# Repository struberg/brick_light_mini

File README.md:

# Lightning system for game bricks

This is a game brick compatible lightning solution to control 4 LEDs.
The repo contains the controller box source code, schematic and PCB plus all the 3d printer models to create your own enclousure and lamps.
The PCB is deliberately single sided and can easily be etched by yourself with Natriumpersulfate.
Ofc if someone likes to create a double sided PCB to be made at Aisler etc then don't hesitate to ship a PR.

The schematic is based on a 0-series ATtiny-402, but a 202 will likely do fine as well.
A rechargable LiIon LIR2450 acts as power source.
The 2450 size is a good compromise between juice and size. 
Connectors are simple 2x1 Dupont types.

The only somewhat non-jellybean part is the 4x220R 0603 resistor array. 
I had to use it because 4 separate resistors would have been too big to fit on the PCB.
You can get those for very cheap from aliexpress or mouser though.

## How to connect the LEDs

You can use any standard low power white or colored LEDs.
The maximum output per LED is around 15 mA.

Place the controler box so that the button is on the lower left side and the LED connectors are on the left upper side.
The top row of the pins is all ground and internally connected.
The lower row of the pins are the positive LED pins, starting with 1 on the left side.

```
  x  x  x  x
  |  |  |  | 
  1  2  3  4  
  |  |  |  |
  x  x  x  x
```
## How to use

* single click: switch LED 1 on or off
* double click: switch LED 2 on or off
* triple click: switch LED 3 on or off
* quadruple click: switch LED 4 on or off

The device will switch off all LEDS and go to sleep after around 5 Minutes of not using the button.
This prevents emptying the battery when one forgets to turn off all lights.
The sleep current is in the µA range, I measured from 0.2µA to 1.5µA
The device will turn on again simply by pressing the button.

Have fun!

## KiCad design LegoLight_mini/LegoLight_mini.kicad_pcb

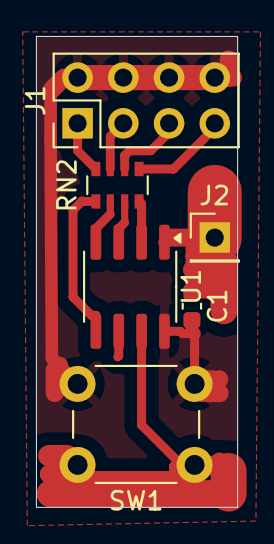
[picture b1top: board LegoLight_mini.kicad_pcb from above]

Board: 2 copper layers, 11.2 x 26.2 mm, 6 parts (0 on the bottom side), 11 nets.

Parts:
C1: 1u; C_0603_1608Metric
J1: Conn_02x04_Odd_Even; PinHeader_2x04_P2.54mm_Vertical
J2: +bat; PinHeader_1x01_P2.54mm_Vertical
RN2: 220R; R_Array_Convex_4x0603
SW1: SW_Push; SW_PUSH_6mm_H7.3mm
U1: ATtiny402-SS; SOIC-8_3.9x4.9mm_P1.27mm

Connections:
/Btn: SW1.1, U1.7 (PA3)
/L1: RN2.1 (R1.1), U1.5 (PA2)
/L2: RN2.2 (R2.1), U1.4 (PA1)
/L3: RN2.3 (R3.1), U1.3 (PA7)
/L4: RN2.4 (R4.1), U1.2 (PA6)
GND: C1.2, J1.2, J1.4, J1.6, J1.8, SW1.2, U1.8 (GND)
unnamed: J1.1, RN2.8 (R1.2)
unnamed: J1.3, RN2.7 (R2.2)
unnamed: J1.5, RN2.6 (R3.2)
unnamed: J1.7, RN2.5 (R4.2)
VCC: C1.1, J2.1, U1.1 (VCC)

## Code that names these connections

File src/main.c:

#include <avr/io.h>
#include <avr/sleep.h>
#include <util/delay.h>
#include <avr/interrupt.h>
#include <stdbool.h>
#include <string.h>

#include "avr_common/strub_common.h"
#include "avr_common/pt.h"



/**
 * @brief small lighting solution for 4 LEDs
 * 
 * L1   PA2 pin5
 * L2   PA1 pin4
 * L3   PA7 pin3
 * L4   PA6 pin2
 * Btn  PA3 pin7
 */

#define BTN_PORT PORTA
#define BTN_PIN PIN3_bm
#define BTN_PIN_CTRL PORTA_PIN3CTRL

#define BTN_SHORT_TIME_MIN 0x05
#define BTN_SHORT_TIME_MAX 0x40
#define BTN_LONG_TIME_MON  0x0120

#define LED_PORT PORTA
#define LED_1_PIN PIN2_bm
#define LED_2_PIN PIN1_bm
#define LED_3_PIN PIN7_bm
#define LED_4_PIN PIN6_bm

#define TASK_TIMEOUT_bm    0x02
#define TASK_INPUT_bm  0x04
#define TASK_ADC_bm    0x08

#define SHUTDODWN_TIME 0xFF00;

volatile uint8_t taskTriggered = 0; 



void setup_cpu(void) {
    // auf prescaler /16 stellen
    // damit rennt die CPU dann effektiv auf 1,33 MHz
    // attention, this needs the CCP (Configuration Change Protection) procedure!

    CCP = CCP_IOREG_gc;
    CLKCTRL.MCLKCTRLB = (0x03 << 1) | 0x01; // clk / 16

    CLKCTRL.MCLKCTRLA = 0x00;
}


void setup_task_timer(void) {
    TASK_TIMER.CCMP = TASK_TIMER_OVERFLOW; /* Compare or Capture */

    TASK_TIMER.CTRLB = 0 | TCB_CNTMODE_INT_gc; // stick at periodic interrupt mode

    TASK_TIMER.CTRLA = TCB_CLKSEL_CLKDIV1_gc  /* CLK_PER (without Prescaler) */
                    | 1 << TCB_ENABLE_bp   /* Enable: enabled */
                    | 0 << TCB_RUNSTDBY_bp /* Run Standby: disabled */
                    | 0 << TCB_SYNCUPD_bp; /* Synchronize Update: disabled */


    // enable Overflow Interrupt. TOP is CCMP
    TASK_TIMER.INTCTRL = TCB_CAPT_bm;
}

volatile uint16_t timers[3] = {0,};

/**
 * @brief TimerB0 overflow
 * 
 * Setzt die 'taskTriggered' bitmask auf FF.
 * Jeder Task kann dann selber checken ob er schon dran war 
 * indem er ein bit darin repräsentiert.
 */
ISR (TCB0_INT_vect) {
    for (uint8_t i=0; i< 3; i++) {
        if (timers[i] > 0) {
            timers[i]--;
        }
    }
    taskTriggered = 0xFF;

    // special handling in the new tinys. one needs to reset the int flags manually 
    TCB0.INTFLAGS = TCB_CAPT_bm;
}

/**
 * @brief wake up from power down
 */
ISR(PORTA_PORT_vect) {
    // clear any subsequent int flag on the pin

    BTN_PORT.INTFLAGS = 0xFF; // writing 1 will clear the int flags

    // disable the PIN interrupt
    BTN_PIN_CTRL &= ~0x03;
}

void setup_io(void) {
    // set leds to output

    LED_PORT.DIRSET = LED_1_PIN | LED_2_PIN | LED_3_PIN | LED_4_PIN;

    // Button input
    BTN_PORT.DIRCLR = BTN_PIN;
    BTN_PIN_CTRL = PORT_PULLUPEN_bm;
}

void setup_adc(void) {
    // setup the voltage reference
    // only used for measuring the VDD itself
    VREF.CTRLA = VREF_ADC0REFSEL_1V5_gc;
    VREF.CTRLB = VREF_ADC0REFEN_bm;

    // ADC itself
    ADC0.CTRLB = 0; // no accumulation

    ADC0.CTRLC = ADC_REFSEL_VDDREF_gc | ADC_PRESC_DIV256_gc;

    ADC0.CTRLD = ADC_INITDLY_DLY64_gc;

    ADC0.MUXPOS = ADC_MUXPOS_INTREF_gc;

    ADC0.CTRLA =  ADC_RESSEL_10BIT_gc | ADC_ENABLE_bm;
}

void adc_enable(void) {
    ADC0.CTRLA |= ADC_ENABLE_bm;
}

void adc_disable(void) {
    ADC0.CTRLA &= ~ADC_ENABLE_bm;
}

void adc_start(void) {
    ADC0.COMMAND |= ADC_STCONV_bm;
}

bool adc_finished(void) {
    return ADC0.INTFLAGS & ADC_RESRDY_bm;
}


void enable_pin_change_interrupt(void) {
    // disable the PIN interrupt
    BTN_PORT.INTFLAGS = 0xFF;
    BTN_PIN_CTRL = PORT_PULLUPEN_bm | PORT_ISC_BOTHEDGES_gc;
}

void disable_pin_change_interrupt(void) {
    // disable the PIN interrupt
    BTN_PIN_CTRL &= ~0x07;
}


void power_down(void) {
    LED_PORT.OUTCLR = LED_1_PIN | LED_2_PIN | LED_3_PIN | LED_4_PIN;

    set_sleep_mode(SLEEP_MODE_PWR_DOWN);
    sleep_enable();
    enable_pin_change_interrupt();
    sleep_cpu();
    sleep_disable();
    disable_pin_change_interrupt();
}


void executeCommand(uint8_t command) {
    // reset timeout;
    timers[0] = SHUTDODWN_TIME;

    switch (command) {
        case 1:
            LED_PORT.OUTTGL = LED_1_PIN;
            break;
        case 2:
            LED_PORT.OUTTGL = LED_2_PIN;
            break;
        case 3:
            LED_PORT.OUTTGL = LED_3_PIN;
            break;
        case 4:
            LED_PORT.OUTTGL = LED_4_PIN;
            break;
    
        default:
            break;
    }

    timers[1] = 0xFFFF;
}

bool buttonPressed(void) {
    return !(BTN_PORT.IN & BTN_PIN);
}

void task_input(void) {
    static uint16_t btnOnTime = 0;
    static uint16_t btnOffTime = 0;
    static uint8_t btnClicks = 1;
    
    if (taskTriggered & TASK_INPUT_bm) {
        taskTriggered &= ~TASK_INPUT_bm;

        if (buttonPressed()) {
            btnOnTime++;

            if (btnOffTime > 0) {
                if (btnOffTime < BTN_SHORT_TIME_MAX) {
                    btnClicks++;
                }
                else {
                    btnClicks = 1;
                }

                btnOffTime = 0;
            }
        }
        else {
            if (btnOnTime > 0 && btnOffTime > BTN_SHORT_TIME_MAX) {
                executeCommand(btnClicks);
                btnOnTime = 0;
                btnOffTime = 0;
            }
            if (btnOffTime < 0xFFFF) {
                btnOffTime++;
            }
        }

    }
}

struct t_adc_state {
    struct pt pt;
    uint8_t blink;
    uint16_t timer;
} adc_state = {0,};


PT_THREAD(task_adc(void)) {
    PT_BEGIN(&adc_state.pt);

    if (taskTriggered & TASK_ADC_bm) {
        // only once per timer interrupt
        taskTriggered &= ~TASK_ADC_bm;
        if (adc_state.timer > 0) {
            adc_state.timer--;
            PT_YIELD(&adc_state.pt);
        }            
        adc_state.timer = 50;

        adc_enable();
        adc_start();


        PT_YIELD_UNTIL(&adc_state.pt, adc_finished());

        uint16_t val = ADC0.RES;
        adc_disable();

        if (val >= 500) {
            // Vdd < 3V now
            // let's start a short blink, then turn off
            LED_PORT.OUTSET = LED_1_PIN | LED_2_PIN | LED_3_PIN | LED_4_PIN;
            timers[1] = 50;
            PT_YIELD_UNTIL(&adc_state.pt, timers[1] == 0);

            power_down();
        }
    }
    
    PT_END(&adc_state.pt);
}

void task_timeout(void) {
    if (taskTriggered & TASK_TIMEOUT_bm) {
        // only once per timer interrupt
        taskTriggered &= ~TASK_TIMEOUT_bm;

        if (timers[0] == 0) {
            power_down();
            timers[0] = SHUTDODWN_TIME;
        }
    }
}

int main(void) {
    setup_cpu();
    setup_task_timer();

    setup_io();
    setup_adc();


    timers[0] = SHUTDODWN_TIME;

    sei();

    while(1) {
        task_adc();
        task_input();
        task_timeout();
    }

    return 1;
}

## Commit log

2025-03-25 ADC for low bat voltage detection
    In case of Ubat lower 3.1 V we blink all lights
    and switch into standby mode.
2025-09-20 adding freecad models
2025-09-20 adding some pictures to get an idea about the final result
2025-09-20 adding a readme
2025-09-20 improved readme
